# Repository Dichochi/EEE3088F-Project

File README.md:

# EEE3088F-Project RMTDIC001 & NGMPHI006

## Description
This project is for the development and design of a Micro-Muse for EEE3088F 2024. The Micro Mouse contains a sesning Module, Power Module, as well as the main control unit(Mother-Board). The sensing system will sense obstacles in the proximity of the mouse, while the power module is mainly for powering the motors of the mouse and charging the on-board battery of the mouse. 

## Structure
* PCB: The KiCAD Project, Schematics & Layout and Project Libraries
* Firmware: Any software developed for the hardware or instructions on where to find relevant sofware
* Documents: Project documentation and component datasheets
* Production: The gerber files, BOM, Budget, or anything required by the fabrication houses
* Simulation: Any simulation files (eg SPICE) or design stage generated results (Eg matlab or excel) 

## Installation
--To be updated-- 

## Usage
The project documentation can be found in the [Documents](https://github.com/Dichochi/EEE3088F-Project/tree/main/Documents) directory and the files required to produce the PCB can be found in the [Production](https://github.com/Dichochi/EEE3088F-Project/tree/main/Production) directory.

## Contact
* Dichochi Ramotlou- RMTDIC001@myuct.ac.za
* Philasande Ngema - NGMPHI006@myuct.ac.za

## Project Status and Roadmap
This project is actively under developement.

## Authors and Acknowledgement
Authors:
* Dichochi Ramotlou
* Philasande Ngema

## License
[Creative Commons Attribution 4.0 International license](https://choosealicense.com/licenses/cc-by-4.0/)

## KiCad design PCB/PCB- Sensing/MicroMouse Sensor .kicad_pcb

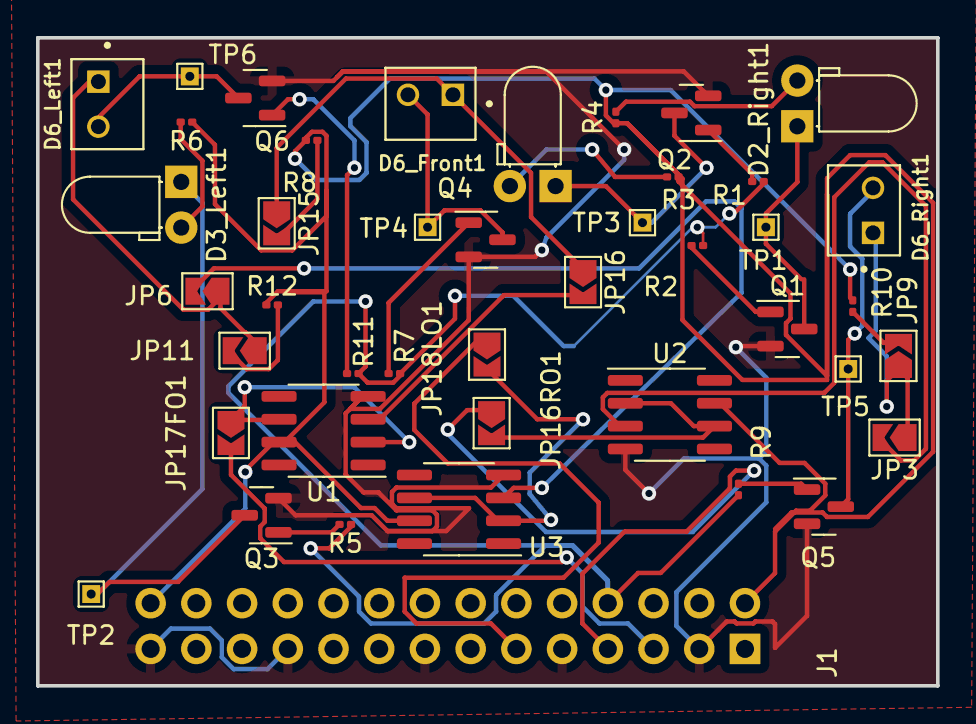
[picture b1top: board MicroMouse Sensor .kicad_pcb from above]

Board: 2 copper layers, 50.0 x 36.0 mm, 43 parts (1 on the bottom side), 33 nets.

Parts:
D1_Front1, D2_Right1, D3_Left1: TSAL4400; LED_D3.0mm_Horizontal_O1.27mm_Z2.0mm_IRBlack
D6_Front1, D6_Left1, D6_Right1: BPW41N; DIO_BPW41N
J1: Conn_02x14_Odd_Even; PinHeader_2x14_P2.54mm_Vertical
JP3, JP6, JP9, JP11, JP15, JP16, JP16RO1, JP17FO1, JP18LO1: Jumper_2_Open; SolderJumper-2_P1.3mm_Open_TrianglePad1.0x1.5mm
Q1, Q2, Q3, Q4, Q5, Q6: C2150; SOT-23
R1, R2, R5, R7, R9, R11: 6.2k; R_0201_0603Metric
R3, R4, R6: 20; R_0201_0603Metric
R8, R10, R12: 300k; R_0201_0603Metric
TP1, TP2, TP3, TP4, TP5, TP6: TestPoint; TestPoint_THTPad_1.0x1.0mm_Drill0.5mm
U1, U2, U3: OP07; SOIC-8_3.9x4.9mm_P1.27mm

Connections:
+3V3: J1.2, J1.28, R3.1, R4.1, R6.1, R8.1, R10.1, R12.1, U1.7 (V+), U2.7 (V+), U3.7 (V+)
Front Out: JP17FO1.1 (A), U1.2 (-), U1.6
Front Sense: D6_Front1.C, JP15.1 (A), JP16.1 (A)
GND: J1.3, J1.9, J1.15, J1.21, J1.27, Q1.2 (E), Q2.2 (E), Q3.2 (E), Q4.2 (E), Q5.2 (E), Q6.2 (E), U1.4 (V-), U2.4 (V-), U3.4 (V-)
Left Out: JP18LO1.2 (B), U3.2 (-), U3.6
Left Sense: D6_Left1.C, JP6.1 (A), JP11.1 (A)
unnamed: D1_Front1.2 (A), R3.2
unnamed: D1_Front1.1 (K), Q2.3 (C), TP3.1
unnamed: D2_Right1.2 (A), R4.2
unnamed: D2_Right1.1 (K), Q1.3 (C), TP1.1
unnamed: D3_Left1.2 (A), R6.2
unnamed: D3_Left1.1 (K), Q3.3 (C), TP2.1
unnamed: J1.5, JP17FO1.2 (B)
unnamed: J1.7, JP16RO1.1 (A)
unnamed: J1.11, JP18LO1.1 (A)
unnamed: JP3.2 (B), U2.3 (+)
unnamed: JP6.2 (B), U3.3 (+)
unnamed: JP9.2 (B), R10.2
unnamed: JP11.2 (B), R12.2
unnamed: JP15.2 (B), R8.2
unnamed: JP16.2 (B), U1.3 (+)
unnamed: Q1.1 (B), R2.2
unnamed: Q2.1 (B), R1.2
unnamed: Q3.1 (B), R5.2
unnamed: Q4.1 (B), R7.2
unnamed: D6_Front1.A, Q4.3 (C), TP4.1
unnamed: Q5.1 (B), R9.2
unnamed: D6_Right1.A, Q5.3 (C), TP5.1
unnamed: Q6.1 (B), R11.2
unnamed: D6_Left1.A, Q6.3 (C), TP6.1
PE15: J1.8, R1.1, R2.1, R5.1, R7.1, R9.1, R11.1
Right Out: JP16RO1.2 (B), U2.2 (-), U2.6
Right Sense: D6_Right1.C, JP3.1 (A), JP9.1 (A)

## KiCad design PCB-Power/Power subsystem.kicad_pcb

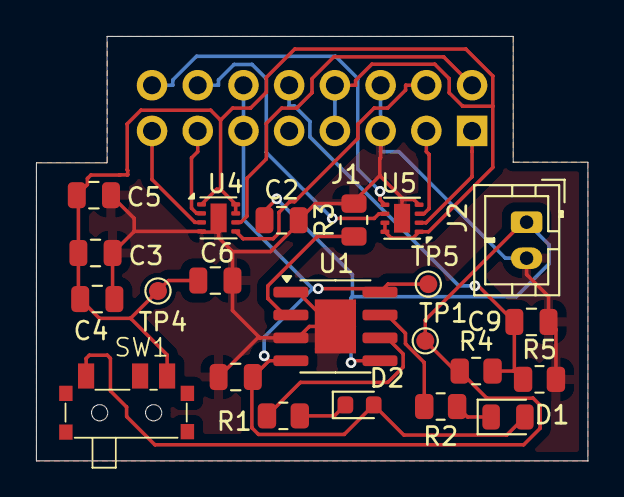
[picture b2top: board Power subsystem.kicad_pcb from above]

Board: 2 copper layers, 30.6 x 23.6 mm, 23 parts (1 on the bottom side), 18 nets.

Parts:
C1, C2: 10uF; C_0805_2012Metric
C3, C4, C5, C6: 100nF; C_0805_2012Metric
C9: 1nF; C_0805_2012Metric
D1: RED; LED_0805_2012Metric
D2: WHITE; LED_0603_1608Metric
J1: Conn_02x08_Odd_Even; PinHeader_2x08_P2.54mm_Vertical
J2: Conn_01x02_Pin; JST_PH_B2B-PH-K_1x02_P2.00mm_Vertical
R1, R2: 1k; R_0805_2012Metric
R3: 3k; R_0805_2012Metric
R4, R5: 100k; R_0805_2012Metric
SW1: SW_SPDT_312; mySwitch
TP1: B+; TestPoint_Pad_D1.0mm
TP4: BATT; TestPoint_Pad_D1.0mm
TP5: +5V; TestPoint_Pad_D1.0mm
U1: TP4056; SOIC-8-1EP_3.9x4.9mm_P1.27mm_EP2.29x3mm
U4, U5: DRV8837; WSON-8-1EP_2x2mm_P0.5mm_EP0.9x1.6mm

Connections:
+5V: C1.1, D1.2 (A), D2.2 (A), J1.11, J1.12, TP5.1, U1.4 (VCC), U1.8 (CE)
B+: C2.1, J2.1, R4.1, SW1.1 (B), TP1.1, U1.5 (BAT)
BATT: C3.1, C4.1, C5.1, C6.1, J1.7, J1.8, SW1.3 (A), TP4.1, U4.1 (VM), U4.7 (~SLEEP), U4.8 (VCC), U5.1 (VM), U5.7 (~SLEEP), U5.8 (VCC)
BATT_ADC: C9.1, J1.10, R4.2, R5.1
GND: C1.2, C2.2, C3.2, C4.2, C5.2, C6.2, C9.2, J1.5, J1.6, J2.2, R3.2, R5.2, U1.1 (TEMP), U1.3 (GND), U1.9 (PP), U4.4 (GND), U4.9 (GND), U5.4 (GND), U5.9 (GND)
M1_A: J1.13, U4.2 (OUT1)
M1_B: J1.15, U4.3 (OUT2)
M1_PWM1: J1.2, U4.6 (IN1)
M1_PWM2: J1.4, U4.5 (IN2)
M2_A: J1.1, U5.2 (OUT1)
M2_B: J1.3, U5.3 (OUT2)
M2_PWM3: J1.14, U5.6 (IN1)
M2_PWM4: J1.16, U5.5 (IN2)
unnamed: D1.1 (K), R2.1
unnamed: D2.1 (K), R1.1
unnamed: R3.1, U1.2 (PROG)
unnamed: R2.2, U1.7 (~CHRG)
unnamed: R1.2, U1.6 (~STDBY)

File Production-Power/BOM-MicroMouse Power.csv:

Comment,Designator,Footprint,LCSC
100nF,C5,C_0805_2012Metric,
100nF,C4,C_0805_2012Metric,
100k,R4,R_0805_2012Metric,
DRV8837,U5,WSON-8-1EP_2x2mm_P0.5mm_EP0.9x1.6mm,
RED,D1,LED_0805_2012Metric,
3k,R3,R_0805_2012Metric,
10uF,C2,C_0805_2012Metric,
100nF,C3,C_0805_2012Metric,
1nF,C9,C_0805_2012Metric,
1k,R1,R_0805_2012Metric,
DRV8837,U4,WSON-8-1EP_2x2mm_P0.5mm_EP0.9x1.6mm,
1k,R2,R_0805_2012Metric,
10uF,C1,C_0805_2012Metric,
100k,R5,R_0805_2012Metric,
SW_SPDT_312,SW1,mySwitch,
100nF,C6,C_0805_2012Metric,
TP4056,U1,SOIC-8-1EP_3.9x4.9mm_P1.27mm_EP2.29x3mm,
WHITE,D2,LED_0603_1608Metric,

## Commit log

2024-04-15 Sensor Gerber Files
2024-04-15 Clearing up Folders
2024-04-16 Datasheets Upload
2024-04-16 File Modifications
2024-04-20 Sensor documents
2024-04-21 Sensor Document
2024-04-21 Power document
2024-04-21 Sorting out files
2024-05-16 Sensor Documents Update
2024-05-16 Sensor code upload
